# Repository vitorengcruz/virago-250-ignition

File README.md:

# virago-250-ignition
A Yamaha Virago 250 - and similar motorcycles - ignition box

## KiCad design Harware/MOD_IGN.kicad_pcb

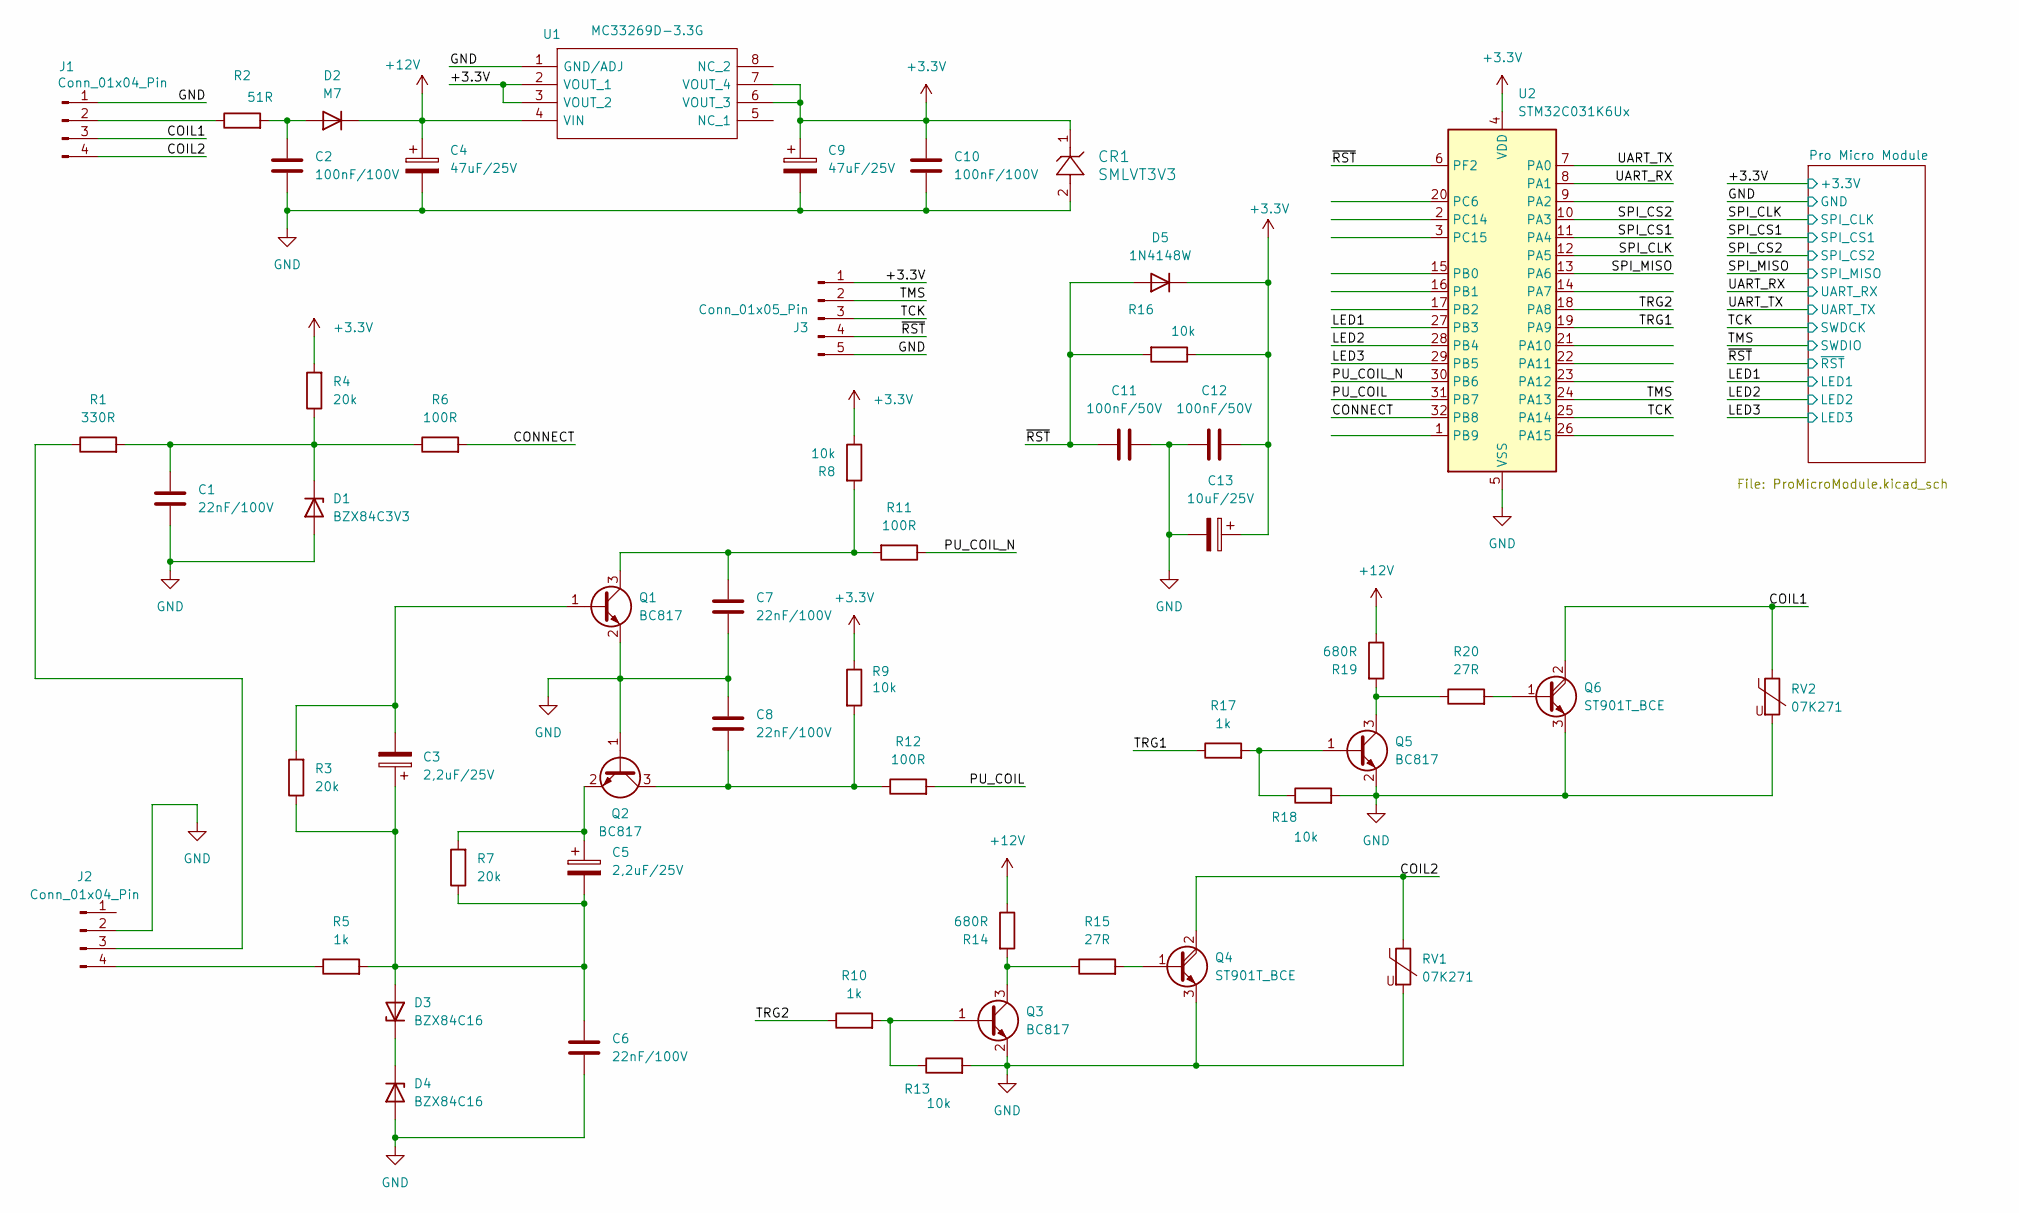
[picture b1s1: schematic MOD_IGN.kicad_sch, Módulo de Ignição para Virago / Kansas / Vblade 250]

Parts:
C1, C6, C7, C8: 22nF/100V; C_0805_2012Metric_Pad1.18x1.45mm_HandSolder
C2, C10: 100nF/100V; C_0805_2012Metric_Pad1.18x1.45mm_HandSolder
C3, C5: 2,2uF/25V; CP_Radial_D5.0mm_P2.00mm
C4, C9: 47uF/25V; CP_Radial_D5.0mm_P2.00mm
C11, C12: 100nF/50V; C_0805_2012Metric_Pad1.18x1.45mm_HandSolder
C13: 10uF/25V; CP_Radial_D5.0mm_P2.00mm
CR1: SMLVT3V3; SMB_STM
D1: BZX84C3V3; SOT-23
D2: M7; D_SMA
D3, D4: BZX84C16; SOT-23
D5: 1N4148W; D_SOD-123
J1, J2: Conn_01x04_Pin; SolderWire-0.1sqmm_1x04_P3.6mm_D0.4mm_OD1mm
J3: Conn_01x05_Pin; PinHeader_1x05_P2.54mm_Vertical
Q1, Q2, Q3, Q5: BC817; SOT-23
Q4, Q6: ST901T_BCE; TO-220-3_Horizontal_HeatSink
R1: 330R; R_0805_2012Metric_Pad1.20x1.40mm_HandSolder
R2: 51R; R_1210_3225Metric_Pad1.30x2.65mm_HandSolder
R3, R4, R7: 20k; R_0805_2012Metric_Pad1.20x1.40mm_HandSolder
R5, R10, R17: 1k; R_0805_2012Metric_Pad1.20x1.40mm_HandSolder
R6, R11, R12: 100R; R_0805_2012Metric_Pad1.20x1.40mm_HandSolder
R8, R9, R13, R16, R18: 10k; R_0805_2012Metric_Pad1.20x1.40mm_HandSolder
R14, R19: 680R; R_0805_2012Metric_Pad1.20x1.40mm_HandSolder
R15, R20: 27R; R_0805_2012Metric_Pad1.20x1.40mm_HandSolder
RV1, RV2: 07K271; RV_Disc_D7mm_W3.8mm_P5mm
U1: MC33269D-3.3G; SOIC127P600X175-8N; Manufacturer_Part_Number MC33269D-3.3G; Mouser Part Number 863-MC33269D-3.3G
U2: STM32C031K6Ux; QFN-32-1EP_5x5mm_P0.5mm_EP3.45x3.45mm

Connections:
+3.3V: C9.1, C10.2, C12.2, C13.1, CR1.1, D5.1 (K), J3.1, R4.2, R8.1, R9.1, R16.1, U1.2 (VOUT_1), U1.3 (VOUT_2), U1.6 (VOUT_3), U1.7 (VOUT_4), U2.4 (VDD); also elsewhere on the board
+12V: C4.1, D2.1 (K), R14.1, R19.1, U1.4 (VIN)
/COIL1: J1.3, Q6.2 (C), RV2.1
/COIL2: J1.4, Q4.2 (C), RV1.1
/CONNECT: R6.2, U2.32 (PB8)
/LED1: U2.27 (PB3); also elsewhere on the board
/LED2: U2.28 (PB4); also elsewhere on the board
/LED3: U2.29 (PB5); also elsewhere on the board
/PU_COIL: R12.2, U2.31 (PB7)
/PU_COIL_N: R11.1, U2.30 (PB6)
/SPI_CLK: U2.12 (PA5); also elsewhere on the board
/SPI_CS1: U2.11 (PA4); also elsewhere on the board
/SPI_CS2: U2.10 (PA3); also elsewhere on the board
/SPI_MISO: U2.13 (PA6); also elsewhere on the board
/TCK: J3.3, U2.25 (PA14); also elsewhere on the board
/TMS: J3.2, U2.24 (PA13); also elsewhere on the board
/TRG1: R17.1, U2.19 (PA9)
/TRG2: R10.1, U2.18 (PA8)
/UART_RX: U2.8 (PA1); also elsewhere on the board
/UART_TX: U2.7 (PA0); also elsewhere on the board
/~RST: C11.2, D5.2 (A), J3.4, R16.2, U2.6 (PF2); also elsewhere on the board
GND: C1.2, C2.1, C4.2, C6.2, C7.2, C8.1, C9.2, C10.1, C11.1, C12.1, C13.2, CR1.2, D1.1 (A), D4.1 (A), J1.1, J2.2, J3.5, Q1.2 (E), Q2.1 (B), Q3.2 (E), Q4.3 (E), Q5.2 (E), Q6.3 (E), R13.2, R18.2, RV1.2, RV2.2, U1.1 (GND/ADJ), U2.5 (VSS), U2.33 (VSS); also elsewhere on the board
unnamed: C1.1, D1.3 (K), R1.2, R4.1, R6.1
unnamed: C2.2, D2.2 (A), R2.2
unnamed: C3.1, C5.2, C6.1, D3.1 (A), R3.1, R5.2, R7.1
unnamed: D3.3 (K), D4.3 (K)
unnamed: J1.2, R2.1
unnamed: J2.3, R1.1
unnamed: J2.4, R5.1
unnamed: C3.2, Q1.1 (B), R3.2
unnamed: C7.1, Q1.3 (C), R8.2, R11.2
unnamed: C8.2, Q2.3 (C), R9.2, R12.1
unnamed: C5.1, Q2.2 (E), R7.2
unnamed: Q3.1 (B), R10.2, R13.1
unnamed: Q3.3 (C), R14.2, R15.1
unnamed: Q4.1 (B), R15.2
unnamed: Q5.1 (B), R17.2, R18.1
unnamed: Q5.3 (C), R19.2, R20.1
unnamed: Q6.1 (B), R20.2

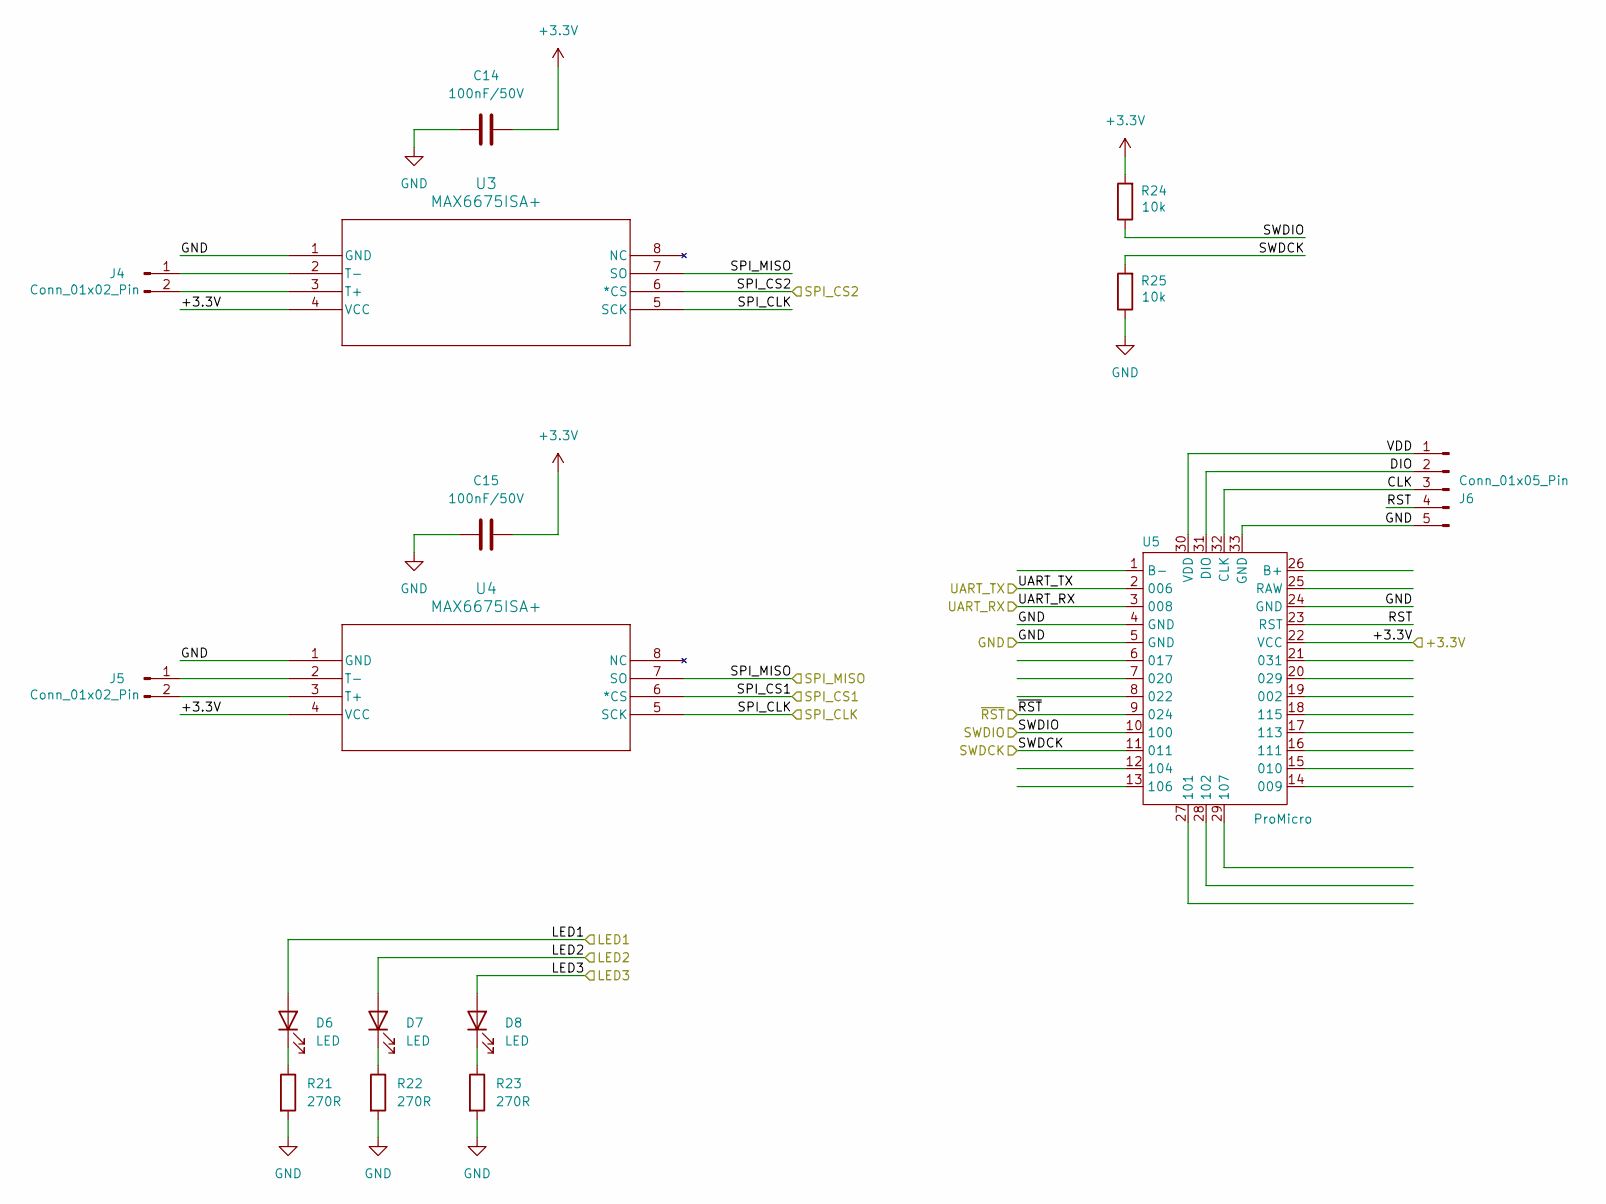
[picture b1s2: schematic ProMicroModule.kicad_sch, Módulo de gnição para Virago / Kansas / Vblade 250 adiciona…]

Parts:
C14, C15: 100nF/50V; C_0805_2012Metric_Pad1.18x1.45mm_HandSolder
D6, D7, D8: LED; LED_0805_2012Metric
J4, J5: Conn_01x02_Pin; Molex_KK-254_AE-6410-02A_1x02_P2.54mm_Vertical
J6: Conn_01x05_Pin; PinHeader_1x05_P2.54mm_Vertical
R21, R22, R23: 270R; R_0805_2012Metric_Pad1.20x1.40mm_HandSolder
R24, R25: 10k; R_0805_2012Metric_Pad1.20x1.40mm_HandSolder
U3, U4: MAX6675ISA+; SOIC127P600X175-8N
U5: ProMicro; SuperMini NRF52840

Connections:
+3.3V: C14.2, C15.2, R24.2, U3.4 (VCC), U4.4 (VCC), U5.22 (VCC); also elsewhere on the board
/LED1: D6.2 (A); also elsewhere on the board
/LED2: D7.2 (A); also elsewhere on the board
/LED3: D8.2 (A); also elsewhere on the board
/Pro Micro Module/CLK: J6.3, U5.32 (CLK)
/Pro Micro Module/DIO: J6.2, U5.31 (DIO)
/Pro Micro Module/RST: J6.4, U5.23 (RST)
/Pro Micro Module/VDD: J6.1, U5.30 (VDD)
/SPI_CLK: U3.5 (SCK), U4.5 (SCK); also elsewhere on the board
/SPI_CS1: U4.6 (*CS); also elsewhere on the board
/SPI_CS2: U3.6 (*CS); also elsewhere on the board
/SPI_MISO: U3.7 (SO), U4.7 (SO); also elsewhere on the board
/TCK: R25.2, U5.11; also elsewhere on the board
/TMS: R24.1, U5.10 (100); also elsewhere on the board
/UART_RX: U5.3 (008); also elsewhere on the board
/UART_TX: U5.2 (006); also elsewhere on the board
/~RST: U5.9 (024); also elsewhere on the board
GND: C14.1, C15.1, J6.5, R21.2, R22.2, R23.2, R25.1, U3.1 (GND), U4.1 (GND), U5.4 (GND), U5.5 (GND), U5.24 (GND), U5.33 (GND); also elsewhere on the board
unnamed: D6.1 (K), R21.1
unnamed: D7.1 (K), R22.1
unnamed: D8.1 (K), R23.1
unnamed: J4.1, U3.2 (T-)
unnamed: J4.2, U3.3 (T+)
unnamed: J5.1, U4.2 (T-)
unnamed: J5.2, U4.3 (T+)

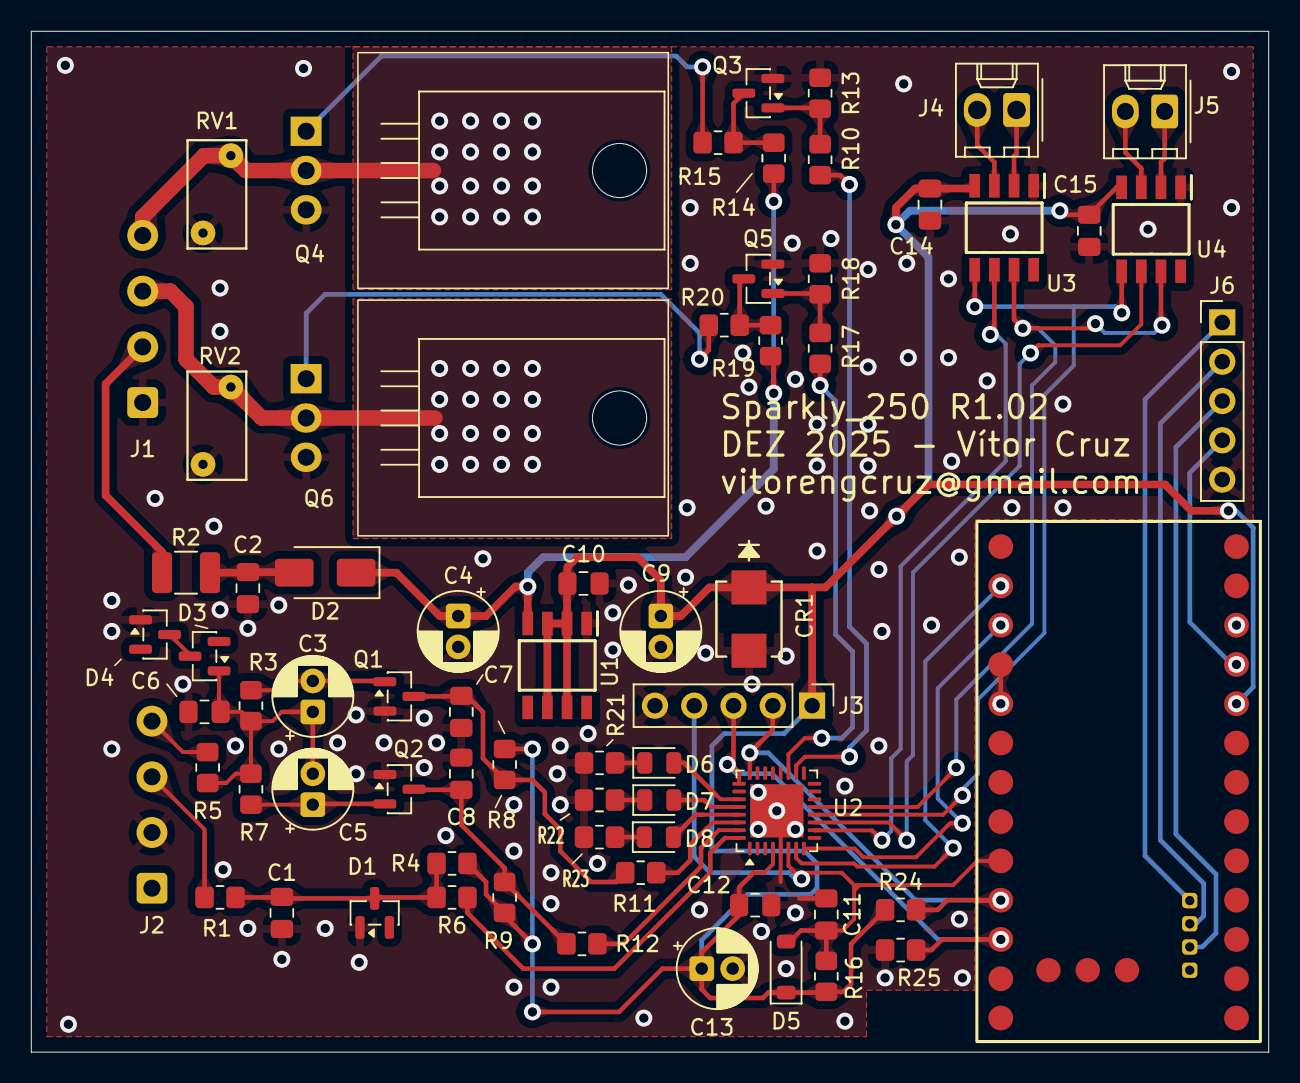
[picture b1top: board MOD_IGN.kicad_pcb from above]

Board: 2 copper layers, 80.0 x 66.0 mm, 68 parts (0 on the bottom side), 50 nets.

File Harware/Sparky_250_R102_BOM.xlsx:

Part Num | Comment | Designator | Footprint | JLCPCB Part #
CC0805KRX7R0BB223 | 100V 22nF X7R ±10% 0805 Multilayer Ceramic Capacitors MLCC - SMD/SMT ROHS | C1, C6, C7, C8 | 0805 SMD | C107137
10uF25V5x11KM | -40℃~+105℃ 10uF 11mm 2000hrs@105℃ 25V 2mm 38mA@120Hz 5mm ±20% Plugin,D5xL11mm A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 | C13 | Radial D5mm P2mm THT | C49304949
CC0805KRX7R9BB104 | 100nF 50V X7R ±10% 0805 Multilayer Ceramic Capacitors MLCC - SMD/SMT ROHS | C2, C10, C11, C12, C14, C15 | 0805 SMD | C49678
KM225M100D11RR0VH2FP0 | 1000hrs@105℃ 100V 11mm 2.2uF 2mm 5mm ±20% Plugin,D5xL11mm Aluminum Electrolytic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 | C3, C5 | Radial D5mm P2mm THT | C10745
KM476M035D11RR0VH2FP0 | 1000hrs@105℃ 11mm 2mm 35V 47uF 5mm ±20% Plugin,D5xL11mm Aluminum Electrolytic C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 | C4, C9 | Radial D5mm P2mm THT | C40063
SMLVT3V3 | 200uA 3.3V 4.1V 50A 600W 7.3V TVS Unidirectional DO-214AA(SMB) ESD and Surge Pr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 | CR1 | SMB SMD | C283619
BZX84C3V3 | -55℃~+150℃ 3.1V~3.5V 3.3V 300mW 5uA@1V 600Ω 95Ω Independent SOT-23 Zener Diodes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 | D1 | SOT-23-3 SMD | C19077467
M7 | -65℃~+150℃ 1.1V@1A 1A 1kV 30A 5uA@1kV SMA(DO-214AC) Diodes - General Purpose RO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 | D2 | SMA SMD | C82443
BZX84C16 | -55℃~+150℃ 100nA 15.3V~17.1V 16V 200Ω 300mW 40Ω Independent SOT-23 Zener Diodes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 | D3, D4 | SOT-23-3 SMD | C22379471
1N4148W | 150mA 1A 1V@50mA 1uA@75V 400mW 4ns 75V Independent SOD-123 Switching Diodes ROHS | D5 | SOD123 SMD | C81598
NCD0805R1 | -30℃~+85℃ 1.6V~2.6V 130° 195mcd 25mA 615nm~630nm 630nm 65mW Discrete Diode Red 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 | D6,D7,D8 | 0805 LED diode SMD | C84256
KH-2.54PH180-1X5P-L11.5 | -40℃~+105℃ 1 1x5P 2.54mm 2.5mm 3A 3mm 5P 6mm Black Pin Header Through Hole Plug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 | J3, J6 | Pin header 2,54mm THT | C2932699
BC817 | 1 NPN 100MHz 100nA 300mW 45V 500mA 5V 600@100mA,1V 700mV NPN SOT-23 Bipolar (BJ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 | Q1, Q2, Q3, Q5 | SOT-23-3 SMD | C466643
ST901T | 1.8V 100W 100uA 1800 2V 350V 4A 5V NPN TO-220 Darlington Transistors ROHS | Q4, Q6 | TO-220-3-Horizontal THT | C2926457
0805W8F3300T5E | -55℃~+155℃ 125mW 150V 330Ω Thick Film Resistor ±1% ±100ppm/℃ 0805 Chip Resistor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 | R1 | 0805 SMD | C17630
0805W8F6800T5E | -55℃~+155℃ 125mW 150V 680Ω Thick Film Resistor ±1% ±100ppm/℃ 0805 Chip Resistor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 | R14, R19 | 0805 SMD | C17798
0805W8F270JT5E | -55℃~+155℃ 125mW 150V 27Ω Thick Film Resistor ±1% ±100ppm/℃ 0805 Chip Resistor 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 | R15, R20 | 0805 SMD | C17594
1206W4F510JT5E | -55℃~+155℃ 200V 250mW 51Ω Thick Film Resistor ±1% ±100ppm/℃ 1206 Chip Resistor 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 | R2 | 1206 SMD | C18019
0805W8F2700T5E | -55℃~+155℃ 125mW 150V 270Ω Thick Film Resistor ±1% ±100ppm/℃ 0805 Chip Resistor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 | R21, R22, R23 | 0805 SMD | C17590
0805W8F2002T5E | -55℃~+155℃ 125mW 150V 20kΩ Thick Film Resistor ±1% ±100ppm/℃ 0805 Chip Resistor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 | R3, R4, R7 | 0805 SMD | C4328
0805W8F1001T5E | -55℃~+155℃ 125mW 150V 1kΩ Thick Film Resistor ±1% ±100ppm/℃ 0805 Chip Resistor 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 | R5, R10, R17 | 0805 SMD | C17513
0805W8F1000T5E | -55℃~+155℃ 100Ω 125mW 150V Thick Film Resistor ±1% ±100ppm/℃ 0805 Chip Resistor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 | R6,R11,R12 | 0805 SMD | C17408
0805W8F1002T5E | -55℃~+155℃ 10kΩ 125mW 150V Thick Film Resistor ±1% ±100ppm/℃ 0805 Chip Resistor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 | R8,R9,R13,R16,R18,R24,R25 | 0805 SMD | C17414
FNR-07K271 | 1.2kA 15J 170pF@1kHz 175V 225V 243V~297V 455V Plugin Varistors ROHS | RV1,RV2 | Disc D7mm W 3.8mm THT | C107478
MC33269DR2-3.3G | -40℃~+125℃ 1 1.35V@(800mA) 20V 3.3V 55dB@(120Hz) 800mA 8mA Fixed Over Current P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 | U1 | SOIC8 SMD | C7301
STM32C031K6U6 | -40℃~+85℃ 12KB 12bit 2V~3.6V 30 32 Bit 32KB 48MHz ARM Cortex-M0+ Built-in+Exter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 | U2 | QFN32 SMD | C5456204
MAX6675ISA+T | -20℃~+85℃ 3V~5.5V SPI SOIC-8 Interface - Specialized ROHS | U3,U4 | SOIC8 SMD | C16030

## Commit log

2026-03-27 Upload V1 hardware to repository.
